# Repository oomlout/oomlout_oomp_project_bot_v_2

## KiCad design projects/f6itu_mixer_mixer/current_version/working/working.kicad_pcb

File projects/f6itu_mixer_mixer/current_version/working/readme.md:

# mixer
 
## summary 
* id: f6itu_mixer_mixer
* user: f6itu
* name: mixer
* board: mixer
* repo: https://github.com/F6ITU/Mixer
* src_file_repo_kicad_pcb: Mixer.kicad_pcb
* src_file_repo_kicad_pcb_link: https://github.com/F6ITU/Mixer/tree/master/Mixer.kicad_pcb

* src_file_repo_sch: Mixer.sch
* src_file_repo_sch_link: https://github.com/F6ITU/Mixer/tree/master/Mixer.sch
* full details link: https://github.com/oomlout/oomlout_oomp_project_bot_v_2/tree/main/projects/f6itu_mixer_mixer/current_version/working

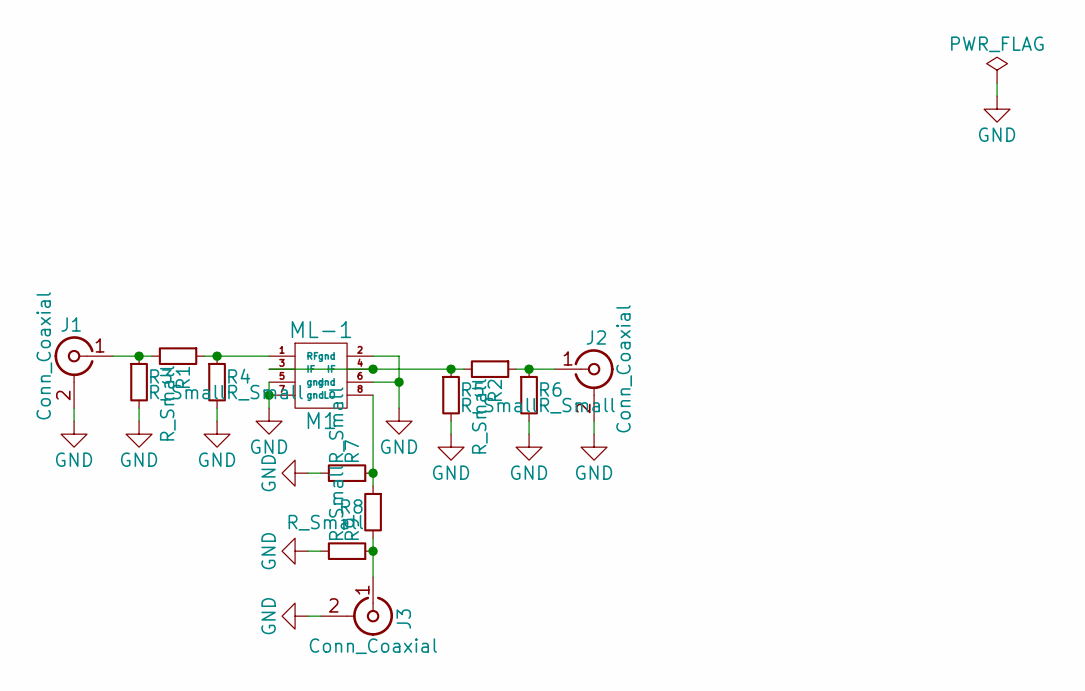
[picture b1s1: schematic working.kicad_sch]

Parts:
J1, J2, J3: Conn_Coaxial; SMA_EDGE_NRW
M1: ML-1
R1, R2, R3, R4, R5, R6, R7, R8, R9: R_Small; R_0805_2012Metric_Pad1.15x1.50mm_HandSolder

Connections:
GND: J1.2 (Ext), J2.2 (Ext), J3.2 (Ext), M1.2 (gnd), M1.5 (gnd), M1.6 (gnd), M1.7 (gnd), R3.2, R4.2, R5.2, R6.2, R7.2, R9.2
unnamed: J1.1 (In), R1.2, R3.1
unnamed: J2.1 (In), R2.1, R6.1
unnamed: J3.1 (In), R8.2, R9.1
unnamed: M1.1 (RF), R1.1, R4.1
unnamed: M1.3 (IF), M1.4 (IF), R2.2, R5.1
unnamed: M1.8 (LO), R7.1, R8.1

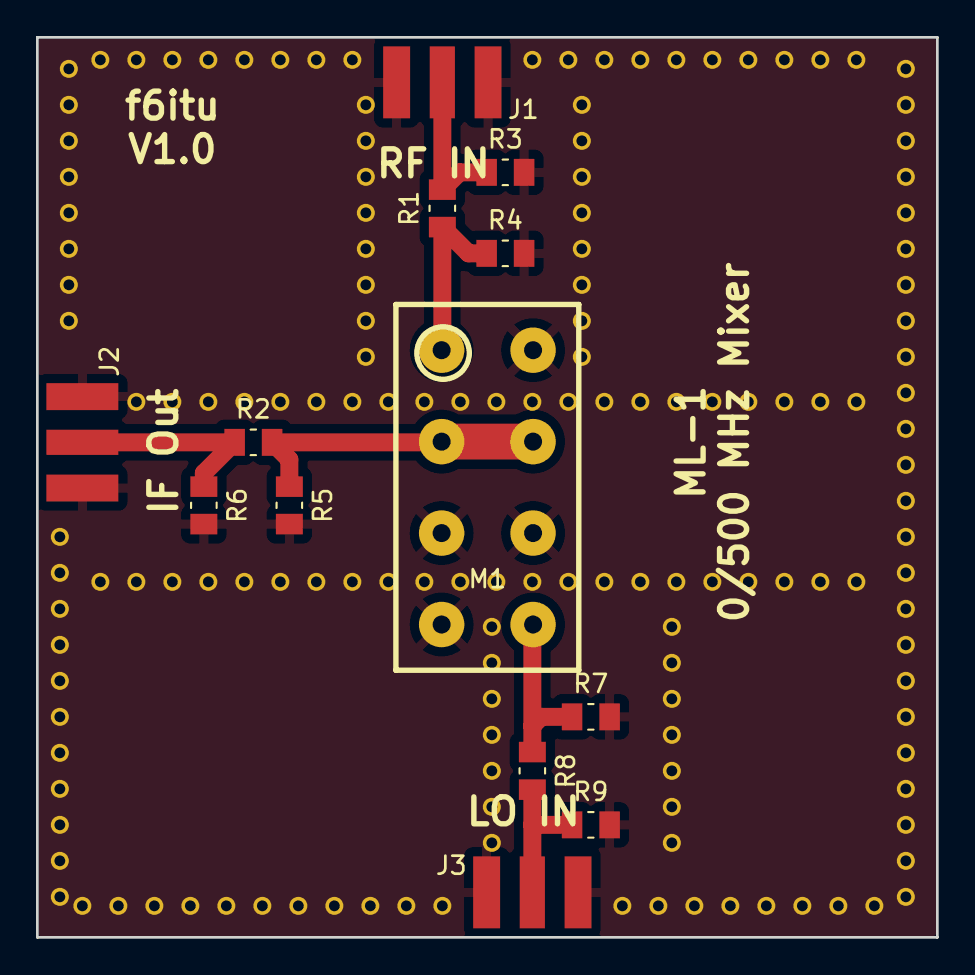
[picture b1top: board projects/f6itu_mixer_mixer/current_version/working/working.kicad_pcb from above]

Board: 2 copper layers, 50.0 x 50.0 mm, 13 parts (0 on the bottom side), 7 nets.

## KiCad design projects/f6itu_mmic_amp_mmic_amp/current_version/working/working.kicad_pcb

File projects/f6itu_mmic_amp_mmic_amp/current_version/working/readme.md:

# mmic_amp
 
## summary 
* id: f6itu_mmic_amp_mmic_amp
* user: f6itu
* name: mmic_amp
* board: mmic_amp
* repo: https://github.com/F6ITU/MMIC_Amp
* src_file_repo_kicad_pcb: MMIC_amp.kicad_pcb
* src_file_repo_kicad_pcb_link: https://github.com/F6ITU/MMIC_Amp/tree/master/MMIC_amp.kicad_pcb

* src_file_repo_sch: MMIC_amp.sch
* src_file_repo_sch_link: https://github.com/F6ITU/MMIC_Amp/tree/master/MMIC_amp.sch
* full details link: https://github.com/oomlout/oomlout_oomp_project_bot_v_2/tree/main/projects/f6itu_mmic_amp_mmic_amp/current_version/working

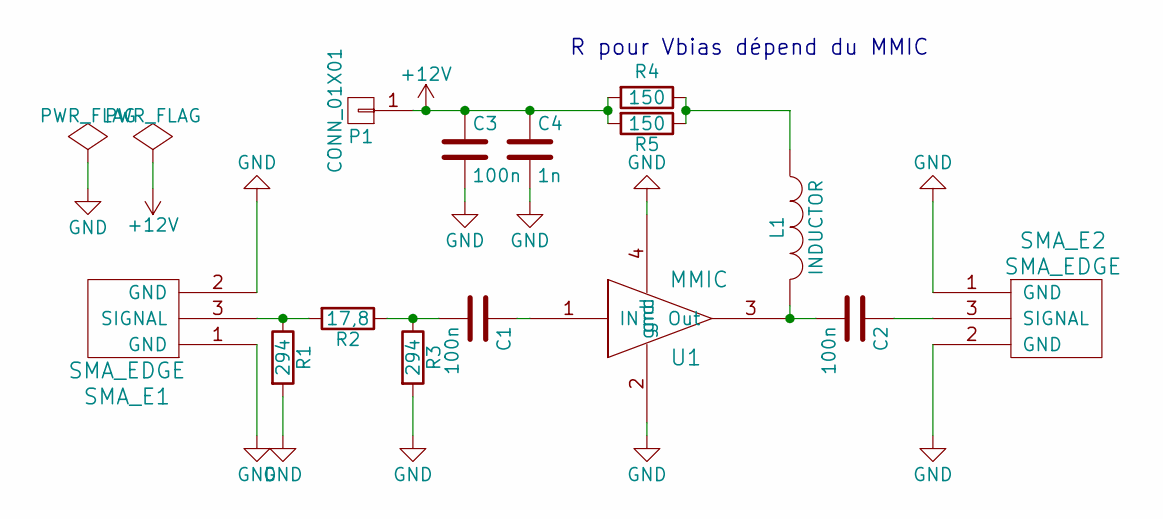
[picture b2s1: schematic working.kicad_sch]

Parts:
C1, C2, C3: 100n; C_1206_HandSoldering
C4: 1n; C_1206_HandSoldering
L1: INDUCTOR; C_1210_HandSoldering
P1: CONN_01X01; 1pin
R1, R3: 294; C_0805_HandSoldering
R2: 17,8; C_0805_HandSoldering
R4, R5: 150; C_0805_HandSoldering
SMA_E1, SMA_E2: SMA_EDGE
U1: MMIC

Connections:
+12V: C3.1, C4.1, P1.1, R4.2, R5.2
GND: C3.2, C4.2, R1.2, R3.2, SMA_E1.1 (GND), SMA_E1.2 (GND), SMA_E2.1 (GND), SMA_E2.2 (GND), U1.2 (gnd), U1.4 (gnd)
unnamed: C1.1, U1.1 (IN)
unnamed: C1.2, R2.1, R3.1
unnamed: C2.1, SMA_E2.3 (SIGNAL)
unnamed: C2.2, L1.2, U1.3 (Out)
unnamed: L1.1, R4.1, R5.1
unnamed: R1.1, R2.2, SMA_E1.3 (SIGNAL)

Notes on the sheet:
R pour Vbias dépend du MMIC

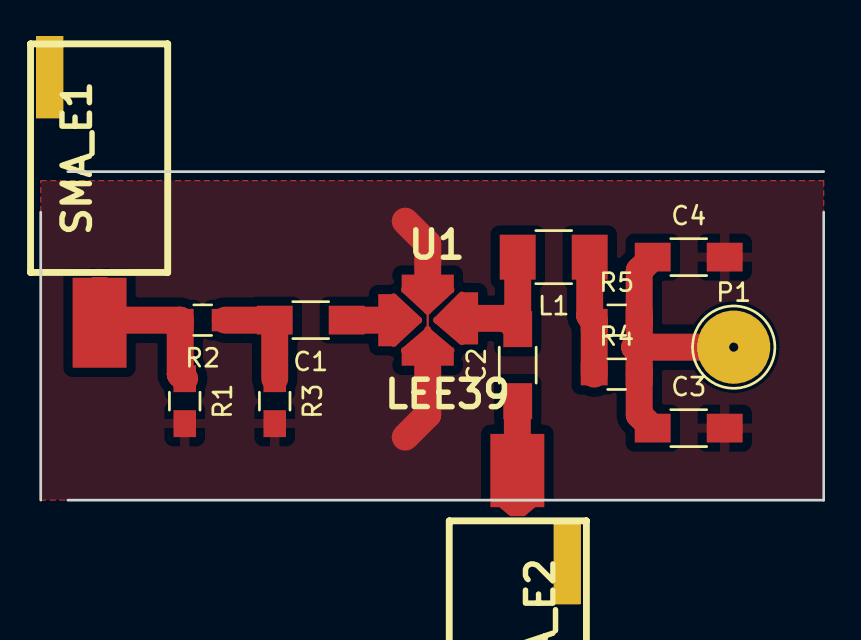
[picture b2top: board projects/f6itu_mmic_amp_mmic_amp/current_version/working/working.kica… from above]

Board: 2 copper layers, 43.5 x 18.2 mm, 14 parts (0 on the bottom side), 8 nets.

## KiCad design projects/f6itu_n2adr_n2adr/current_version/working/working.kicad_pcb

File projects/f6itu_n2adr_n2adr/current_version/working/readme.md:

# n2adr
 
## summary 
* id: f6itu_n2adr_n2adr
* user: f6itu
* name: n2adr
* board: n2adr
* repo: https://github.com/F6ITU/N2ADR
* src_file_repo_kicad_pcb: n2adr.kicad_pcb
* src_file_repo_kicad_pcb_link: https://github.com/F6ITU/N2ADR/tree/master/n2adr.kicad_pcb

* src_file_repo_sch: n2adr.sch
* src_file_repo_sch_link: https://github.com/F6ITU/N2ADR/tree/master/n2adr.sch
* full details link: https://github.com/oomlout/oomlout_oomp_project_bot_v_2/tree/main/projects/f6itu_n2adr_n2adr/current_version/working

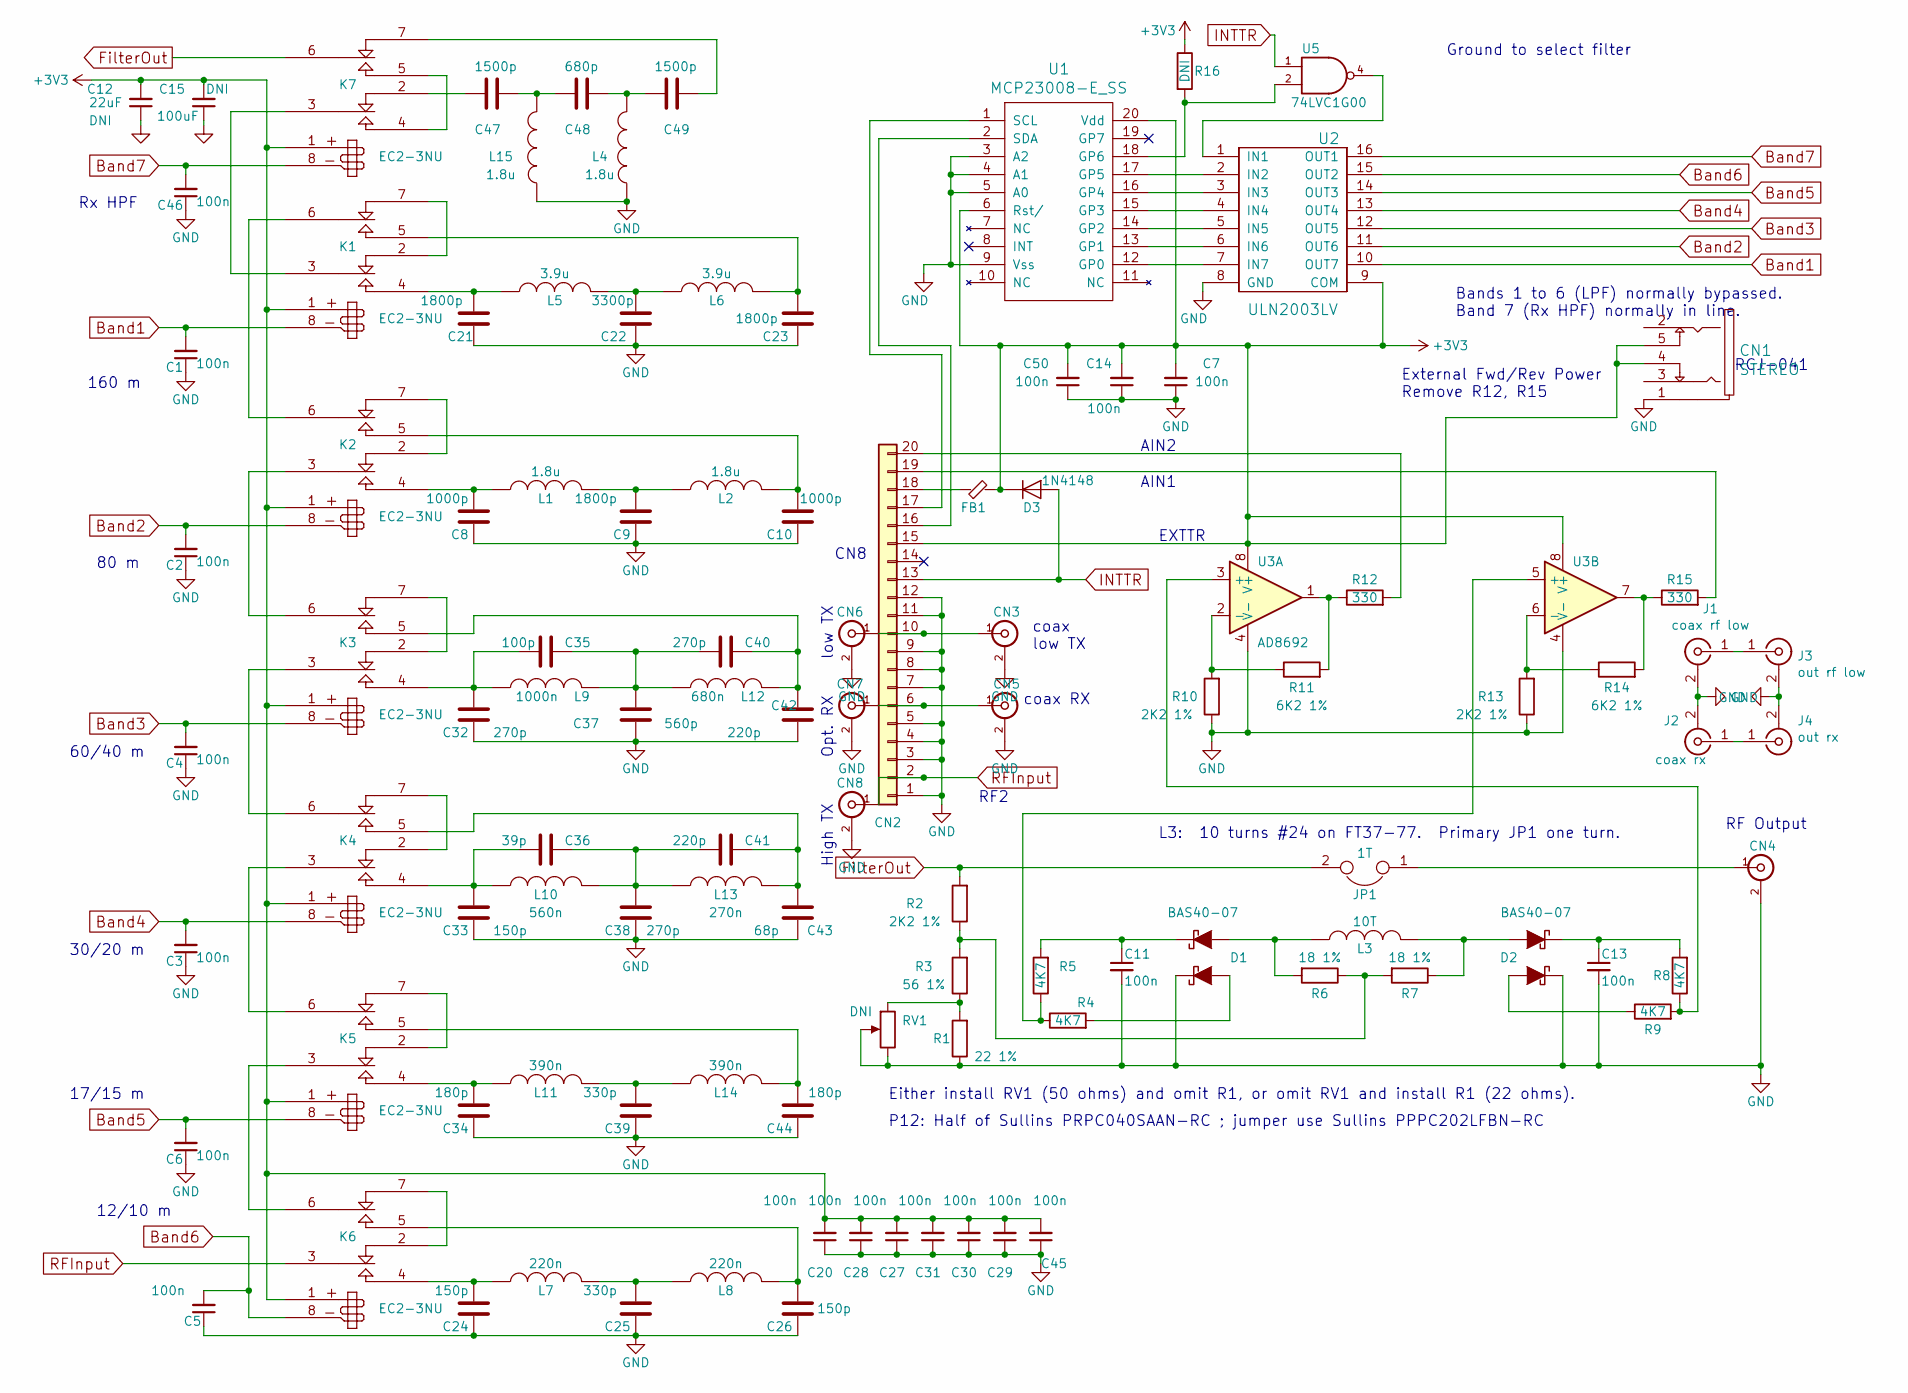
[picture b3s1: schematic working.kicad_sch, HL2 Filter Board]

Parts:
C1, C2, C3, C4, C5, C6, C7, C11, C13, C14, C20, C27, C28, C29, C30, C31, C45, C46, C50: 100n; SMD_0805
C8, C10: 1000p; SMD_1206
C9, C21, C23: 1800p; SMD_1206
C12: 22uF; SMD_0805
C15: 100uF; SMD-1206
C22: 3300p; SMD_1206
C24, C26, C33: 150p; SMD_1206
C25, C39: 330p; SMD_1206
C32, C38, C40: 270p; SMD_1206
C34, C44: 180p; SMD_1206
C35: 100p; SMD_1206
C36: 39p; SMD_1206
C37: 560p; SMD_1206
C41, C42: 220p; SMD_1206
C43: 68p; SMD_1206
C47, C49: 1500p; SMD_0805
C48: 680p; SMD_0805
CN1: STEREO
CN2: Conn_01x20; Pin_Header_Straight_1x20_Pitch2.54mm
CN3: SMA; coax_2mm
CN4, CN6, CN7, CN8: SMA; SMA_EDGE_NRW
CN5: SMA; coax_1mm
D1, D2: BAS40-07; SOT-143
D3: 1N4148; D_SOD-123
FB1: FB; SMD_0805
J1: coax rf low; coax_2mm
J2: coax rx; coax_2mm
J3: out rf low; SMA_EDGE_NRW
J4: out rx; SMA_EDGE_NRW
JP1: 1T; WireConnection_1.20mmDrill
K1, K2, K3, K4, K5, K6, K7: EC2-3NU; RelayDPDT01
L1, L2: 1.8u; SMD_1812
L3: 10T; ToroidT37
L4, L15: 1.8u; SMD_0805
L5, L6: 3.9u; SMD_1812
L7, L8: 220n; SMD_1210
L9: 1000n; SMD_1812
L10: 560n; SMD_1210
L11, L14: 390n; SMD_1210
L12: 680n; SMD_1210
L13: 270n; SMD_1210
R1: 22 1%; SMD_0805
R2, R10, R13: 2K2 1%; SMD_0805
R3: 56 1%; SMD_0805
R4, R5, R8, R9: 4K7; SMD_0805
R6, R7: 18 1%; SMD_0805
R11, R14: 6K2 1%; SMD_0805
R12, R15: 330; SMD_0805
R16: DNI; SMD_0805
RV1: DNI; Trimpot_Bourns_3314G
U1: MCP23008-E_SS; SSOP-20_5.3x7.2mm_P0.65mm
U2: ULN2003LV; TSSOP-16_4.4x5mm_Pitch0.65mm
U3: AD8692; MSOP-8_3x3mm_Pitch0.65mm
U5: 74LVC1G00; SOT-23-5_HandSoldering

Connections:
Band1: C1.2, K1.8, U2.10 (OUT7)
Band2: C2.2, K2.8, U2.11 (OUT6)
Band3: C4.2, K3.8, U2.12 (OUT5)
Band4: C3.2, K4.8, U2.13 (OUT4)
Band5: C6.2, K5.8, U2.14 (OUT3)
Band6: C5.2, K6.8, U2.15 (OUT2)
Band7: C46.2, K7.8, U2.16 (OUT1)
FilterOut: JP1.2, K7.6, R2.2
GND: C1.1, C2.1, C3.1, C4.1, C5.1, C6.1, C7.1, C8.1, C9.1, C10.1, C11.2, C12.1, C13.2, C14.1, C15.1, C20.1, C21.2, C22.2, C23.2, C24.1, C25.1, C26.1, C27.1, C28.1, C29.1, C30.1, C31.1, C32.1, C33.1, C34.1, C37.1, C38.1, C39.1, C42.1, C43.1, C44.1, C45.1, C46.1, C50.1, CN1.1, CN2.1, CN2.3, CN2.4, CN2.5, CN2.7, CN2.8, CN2.9, CN2.11, CN2.12, CN3.2 (Ext), CN4.2 (Ext), CN5.2 (Ext), CN6.2 (Ext), CN7.2 (Ext), CN8.2 (Ext), D1.1 (K), D2.2 (K), J1.2 (Ext), J2.2 (Ext), J3.2 (Ext), J4.2 (Ext), L4.1, L15.1, R1.1, R10.1, R13.1, RV1.2, RV1.3, U1.3 (A2), U1.4 (A1), U1.5 (A0), U1.9 (Vss), U2.8 (GND), U3.4 (V-), U5.3 (GND)
INTTR: CN2.13, D3.2 (A), U5.1
unnamed: C8.2, K2.4, L1.1
unnamed: C9.2, L1.2, L2.1
unnamed: C10.2, K2.5, L2.2
unnamed: C11.1, D1.2 (K), R5.2
unnamed: C13.1, D2.1 (K), R8.2
unnamed: C21.1, K1.4, L5.1
unnamed: C22.1, L5.2, L6.1
unnamed: C23.1, K1.5, L6.2
unnamed: C24.2, K6.4, L7.1
unnamed: C25.2, L7.2, L8.1
unnamed: C26.2, K6.5, L8.2
unnamed: C32.2, C35.2, K3.4, L9.1
unnamed: C33.2, C36.2, K4.4, L10.1
unnamed: C34.2, K5.4, L11.1
unnamed: C35.1, C37.2, C40.2, L9.2, L12.1
unnamed: C36.1, C38.2, C41.2, L10.2, L13.1
unnamed: C39.2, L11.2, L14.1
unnamed: C40.1, C42.2, K3.5, L12.2
unnamed: C41.1, C43.2, K4.5, L13.2
unnamed: C44.2, K5.5, L14.2
unnamed: C47.1, C48.2, L15.2
unnamed: C47.2, K7.2
unnamed: C48.1, C49.2, L4.2
unnamed: C49.1, K7.7
unnamed: CN2.6, CN5.1 (In), CN7.1 (In)
unnamed: CN2.10, CN3.1 (In), CN6.1 (In)
unnamed: CN2.16, U1.2 (SDA)
unnamed: CN2.17, U1.1 (SCL)
unnamed: CN2.18, FB1.2
unnamed: CN2.19, R15.2
unnamed: CN2.20, R12.2
unnamed: CN4.1 (In), JP1.1
unnamed: D1.3 (A), L3.1, R6.2
unnamed: D1.4 (A), R4.2
unnamed: D2.3 (A), R9.1
unnamed: D2.4 (A), L3.2, R7.1
unnamed: J1.1 (In), J3.1 (In)
unnamed: J2.1 (In), J4.1 (In)
unnamed: K1.2, K1.7
unnamed: K1.3, K7.3
unnamed: K1.6, K2.6
unnamed: K2.2, K2.7
unnamed: K2.3, K3.6
unnamed: K3.2, K3.7
unnamed: K3.3, K4.6
unnamed: K4.2, K4.7
unnamed: K4.3, K5.6
unnamed: K5.2, K5.7
unnamed: K5.3, K6.6
unnamed: K6.2, K6.7
unnamed: K7.4, K7.5
unnamed: R1.2, R3.1, RV1.1
unnamed: R2.1, R3.2, R6.1, R7.2
unnamed: R4.1, R5.1, U3.5 (+)
unnamed: R8.1, R9.2, U3.3 (+)
unnamed: R10.2, R11.1, U3.2 (-)
unnamed: R11.2, R12.1, U3.1
unnamed: R13.2, R14.1, U3.6 (-)
unnamed: R14.2, R15.1, U3.7
unnamed: R16.2, U1.18 (GP6), U5.2
unnamed: U1.12 (GP0), U2.7 (IN7)
unnamed: U1.13 (GP1), U2.6 (IN6)
unnamed: U1.14 (GP2), U2.5 (IN5)
unnamed: U1.15 (GP3), U2.4 (IN4)
unnamed: U1.16 (GP4), U2.3 (IN3)
unnamed: U1.17 (GP5), U2.2 (IN2)
unnamed: U2.1 (IN1), U5.4
RFInput: CN2.2, CN8.1 (In), K6.3

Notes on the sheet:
External Fwd/Rev Power Remove R12, R15
RF2
Bands 1 to 6 (LPF) normally bypassed. Band 7 (Rx HPF) normally in line.
CN8
coax low TX
80 m
Opt. RX
L3: 10 turns #24 on FT37-77. Primary JP1 one turn.
low TX
12/10 m
coax RX
30/20 m
AIN1
Ground to select filter
17/15 m
160 m
RCJ-041
60/40 m
EXTTR
AIN2
High TX
Either install RV1 (50 ohms) and omit R1, or omit RV1 and install R1 (22 ohms).
P12: Half of Sullins PRPC040SAAN-RC ; jumper use Sullins PPPC202LFBN-RC
Rx HPF
RF Output

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
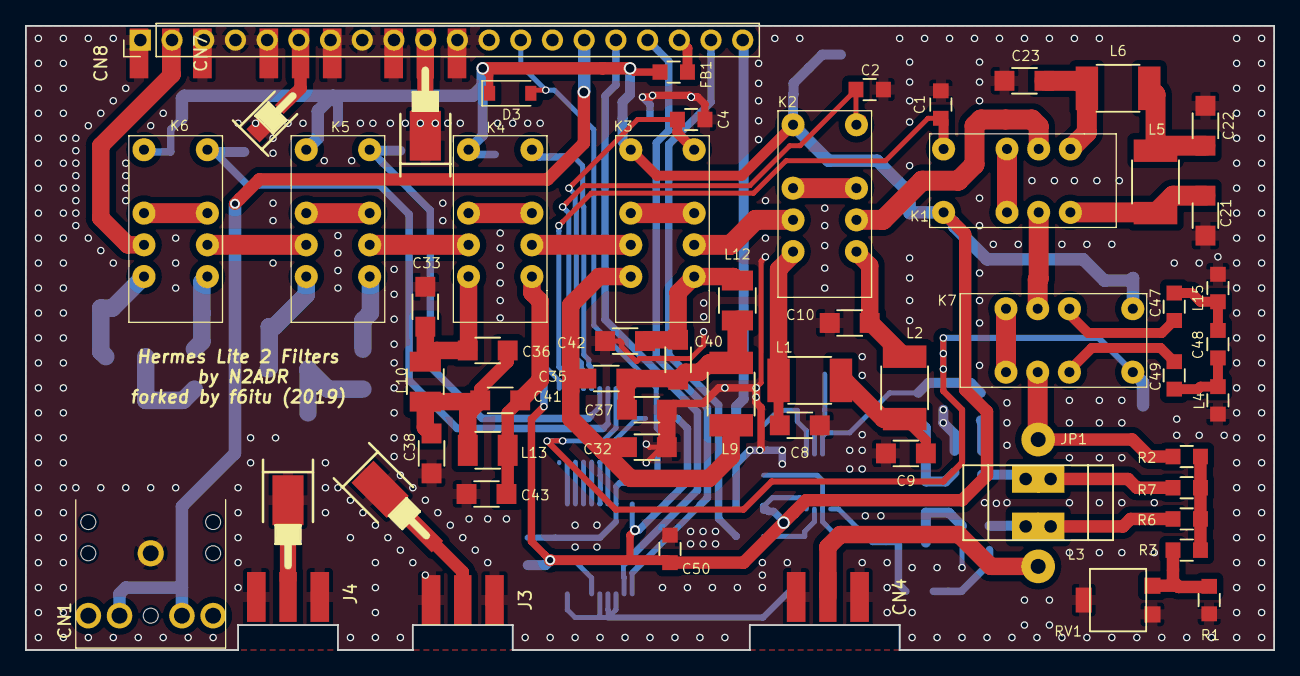
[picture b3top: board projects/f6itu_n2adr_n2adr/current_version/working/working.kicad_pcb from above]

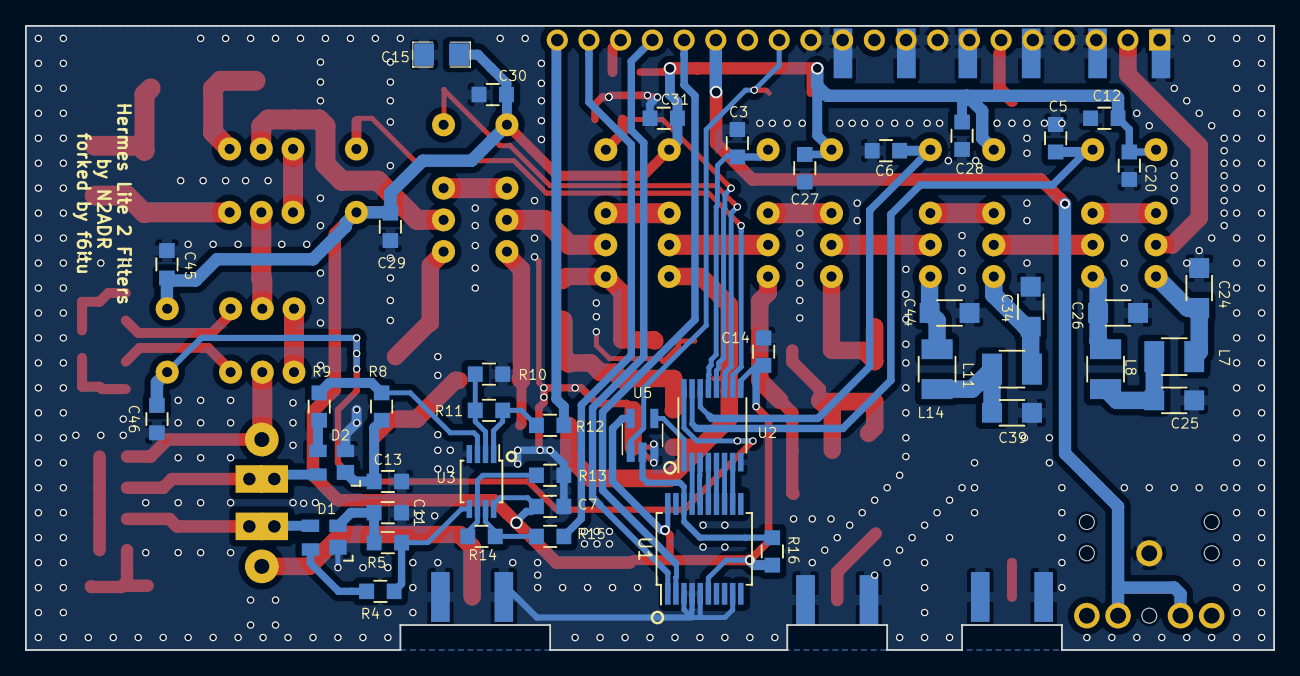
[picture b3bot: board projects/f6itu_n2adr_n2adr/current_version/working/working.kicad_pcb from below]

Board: 4 copper layers, 100.0 x 50.0 mm, 106 parts (44 on the bottom side), 80 nets.
